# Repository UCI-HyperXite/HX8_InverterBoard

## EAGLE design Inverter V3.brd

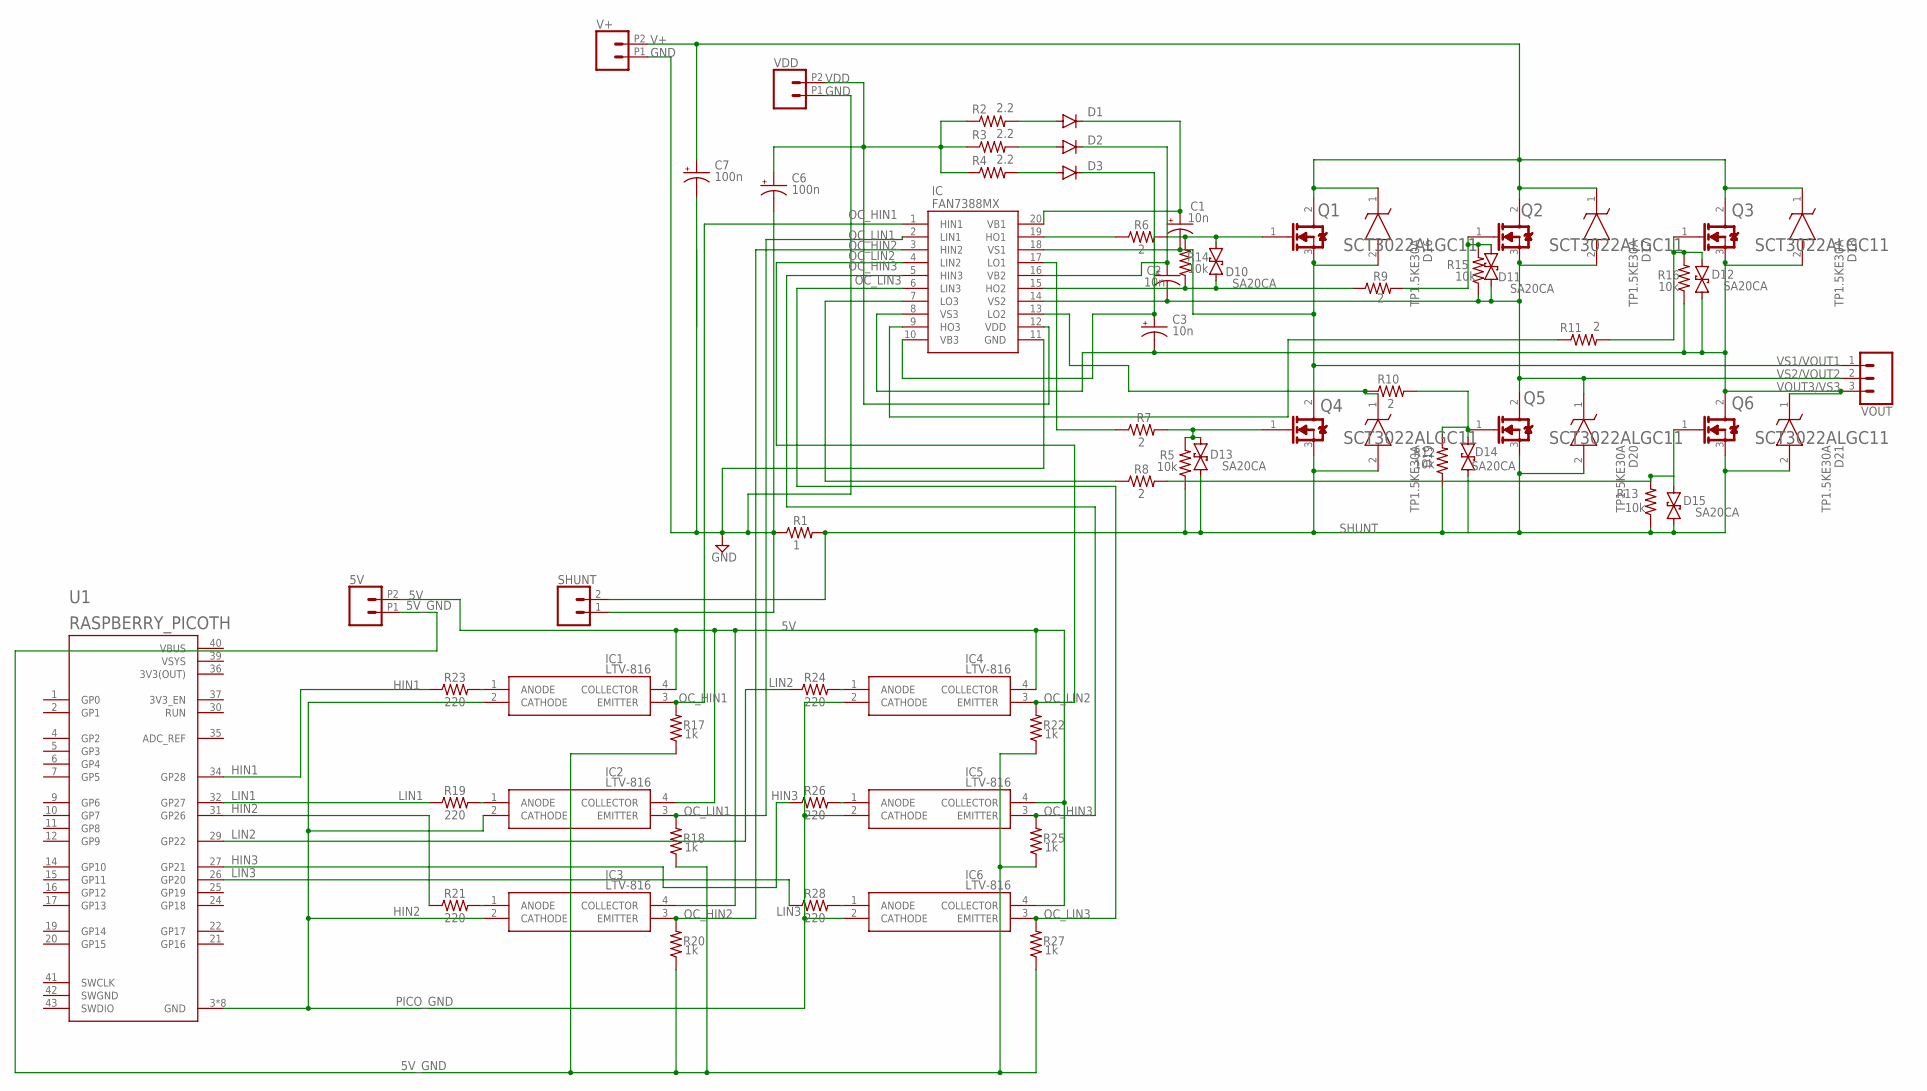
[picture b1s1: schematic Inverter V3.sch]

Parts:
5V: CONN_022.54MM_SCREWTERM; 1X02_2.54_SCREWTERM
C1, C2, C3: 10n; SMC_Z
C6: 100n; SMC_Z
C7: 100n; E5-5
D1, D2, D3: DIODE-GF1; GF1
D10, D11, D12, D13, D14, D15: SA20CA; CB417-15
D16, D17, D18, D19, D20, D21: TP1.5KE30A; DIOAD2855W107L835D505
IC: FAN7388MX; SOIC127P1032X265-20N
IC1, IC2, IC3, IC4, IC5, IC6: LTV-816; DIP762W60P254L460H450Q4N
Q1, Q2, Q3, Q4, Q5, Q6: ROHM_SCT3022ALGC11ROHM_SCT3022ALGC11_0_0; ROHM_SCT3022ALGC11_0
R1: 1; 0207/10
R2, R3, R4: 2.2; 0603
R5, R12, R13, R14, R15, R16: 10k; 0603
R6, R7, R8, R9, R10, R11: 2; 0603
R17, R18, R20, R22, R25, R27: 1k; 0603
R19, R21, R23, R24, R26, R28: 220; 0603
SHUNT: CONN_02PTH4; 1X02_XTRA_BIG
U1: RASPBERRY_PICOTH; PICO-PKG-TH
V+: CONN_022.54MM_SCREWTERM; 1X02_2.54_SCREWTERM
VDD: CONN_022.54MM_SCREWTERM; 1X02_2.54_SCREWTERM
VOUT: CONN_03SCREW-NS; SCREWTERMINAL-3.5MM-3-NS

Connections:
3V3(OUT): U1.36 (3V3(OUT))
5V: 5V.P2 (2), IC1.4 (COLLECTOR), IC2.4 (COLLECTOR), IC3.4 (COLLECTOR), IC4.4 (COLLECTOR), IC5.4 (COLLECTOR), IC6.4 (COLLECTOR)
5V_GND: 5V.P1 (1), R17.1, R18.1, R20.1, R22.1, R25.1, R27.1
GND: C6.-, C7.-, IC.11 (GND), R1.1, SHUNT.1, V+.P1 (1), VDD.P1 (1)
HIN1: R23.1, U1.34 (GP28)
HIN2: R21.1, U1.31 (GP26)
HIN3: R26.1, U1.27 (GP21)
HO1: IC.19 (HO1), R6.1
HO2: D10.A (1), IC.15 (HO2), R9.1, R14.1
HO3: IC.9 (HO3), R11.1
LIN1: R19.1, U1.32 (GP27)
LIN2: R24.1, U1.29 (GP22)
LIN3: R28.1, U1.26 (GP20)
LO1: IC.17 (LO1), R7.1
LO2: D19.1 (K), IC.13 (LO2), R10.1
LO3: IC.7 (LO3), R8.1
unnamed: IC3.1 (ANODE), R21.2
unnamed: IC2.1 (ANODE), R19.2
unnamed: IC1.1 (ANODE), R23.2
unnamed: IC4.1 (ANODE), R24.2
unnamed: IC5.1 (ANODE), R26.2
unnamed: IC6.1 (ANODE), R28.2
unnamed: D1.A, R2.2
unnamed: D2.A, R3.2
unnamed: D3.A, R4.2
OC_HIN1: IC.1 (HIN1), IC1.3 (EMITTER), R17.2
OC_HIN2: IC.3 (HIN2), IC3.3 (EMITTER), R20.2
OC_HIN3: IC.5 (HIN3), IC5.3 (EMITTER), R25.2
OC_LIN1: IC.2 (LIN1), IC2.3 (EMITTER), R18.2
OC_LIN2: IC.4 (LIN2), IC4.3 (EMITTER), R22.2
OC_LIN3: IC.6 (LIN3), IC6.3 (EMITTER), R27.2
PICO_GND: IC1.2 (CATHODE), IC2.2 (CATHODE), IC3.2 (CATHODE), IC4.2 (CATHODE), IC5.2 (CATHODE), IC6.2 (CATHODE), U1.3 (GND), U1.8 (GND), U1.13 (GND), U1.18 (GND), U1.23 (GND), U1.28 (GND), U1.33 (GND), U1.38 (GND)
SHUNT: D13.A (1), D14.A (1), D15.A (1), D19.2 (A), D20.2 (A), D21.2 (A), Q4.3 (SOURCE), Q5.3 (SOURCE), Q6.3 (SOURCE), R1.2, R5.1, R12.1, R13.1, SHUNT.2
SWGND: U1.42 (SWGND)
V+: C7.+, D16.1 (K), D17.1 (K), D18.1 (K), Q1.2 (DRAIN), Q2.2 (DRAIN), Q3.2 (DRAIN), V+.P2 (2)
VB1: C1.+, D1.C, IC.20 (VB1)
VB2: C2.+, D2.C, IC.16 (VB2)
VB3: C3.+, D3.C, IC.10 (VB3)
VBUS: U1.40 (VBUS)
VDD: C6.+, IC.12 (VDD), R2.1, R3.1, R4.1, VDD.P2 (2)
VGIN1: D10.C (2), Q1.1 (GATE), R6.2, R14.2
VGIN2: D11.C (2), Q2.1 (GATE), R9.2, R15.2
VGIN3: D12.C (2), Q3.1 (GATE), R11.2, R16.2
VGIN4: D13.C (2), Q4.1 (GATE), R5.2, R7.2
VGIN5: D14.C (2), Q5.1 (GATE), R10.2, R12.2
VGIN6: D15.C (2), Q6.1 (GATE), R8.2, R13.2
VOUT3/VS3: C3.-, D12.A (1), D18.2 (A), D21.1 (K), IC.8 (VS3), Q3.3 (SOURCE), Q6.2 (DRAIN), R16.1, VOUT.3
VS1/VOUT1: C1.-, D16.2 (A), IC.18 (VS1), Q1.3 (SOURCE), Q4.2 (DRAIN), VOUT.1
VS2/VOUT2: C2.-, D11.A (1), D17.2 (A), D20.1 (K), IC.14 (VS2), Q2.3 (SOURCE), Q5.2 (DRAIN), R15.1, VOUT.2
VSYS: U1.39 (VSYS)

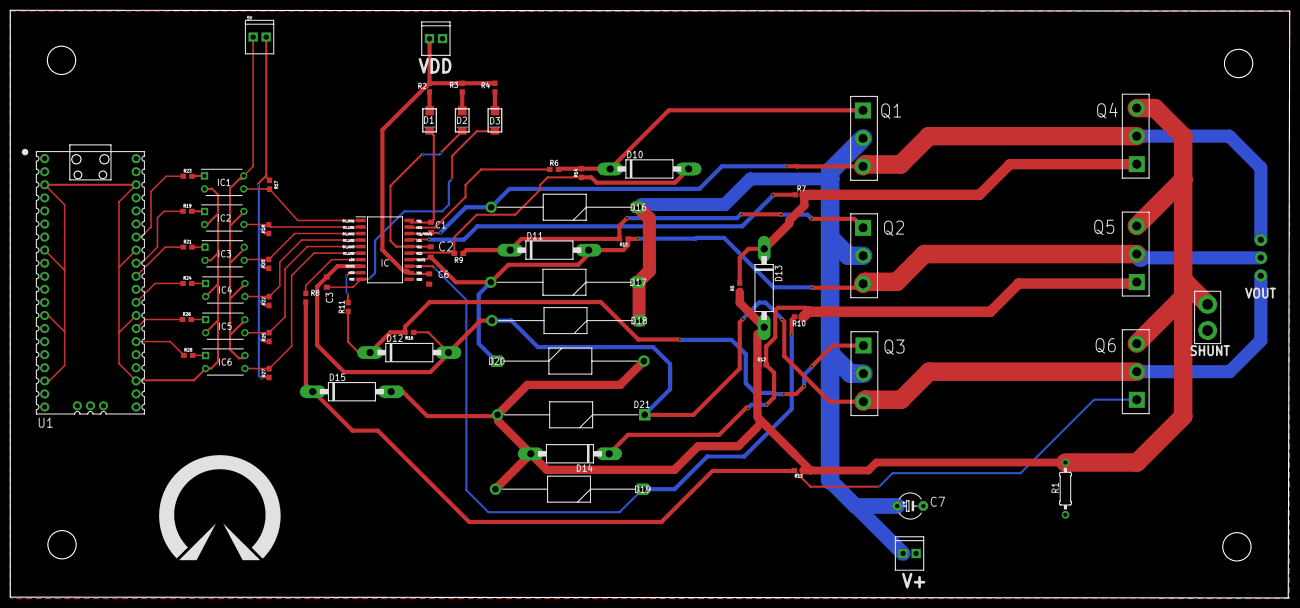
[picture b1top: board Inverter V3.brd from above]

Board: 2 copper layers, 248.6 x 114.2 mm, 67 parts (0 on the bottom side), 46 nets.

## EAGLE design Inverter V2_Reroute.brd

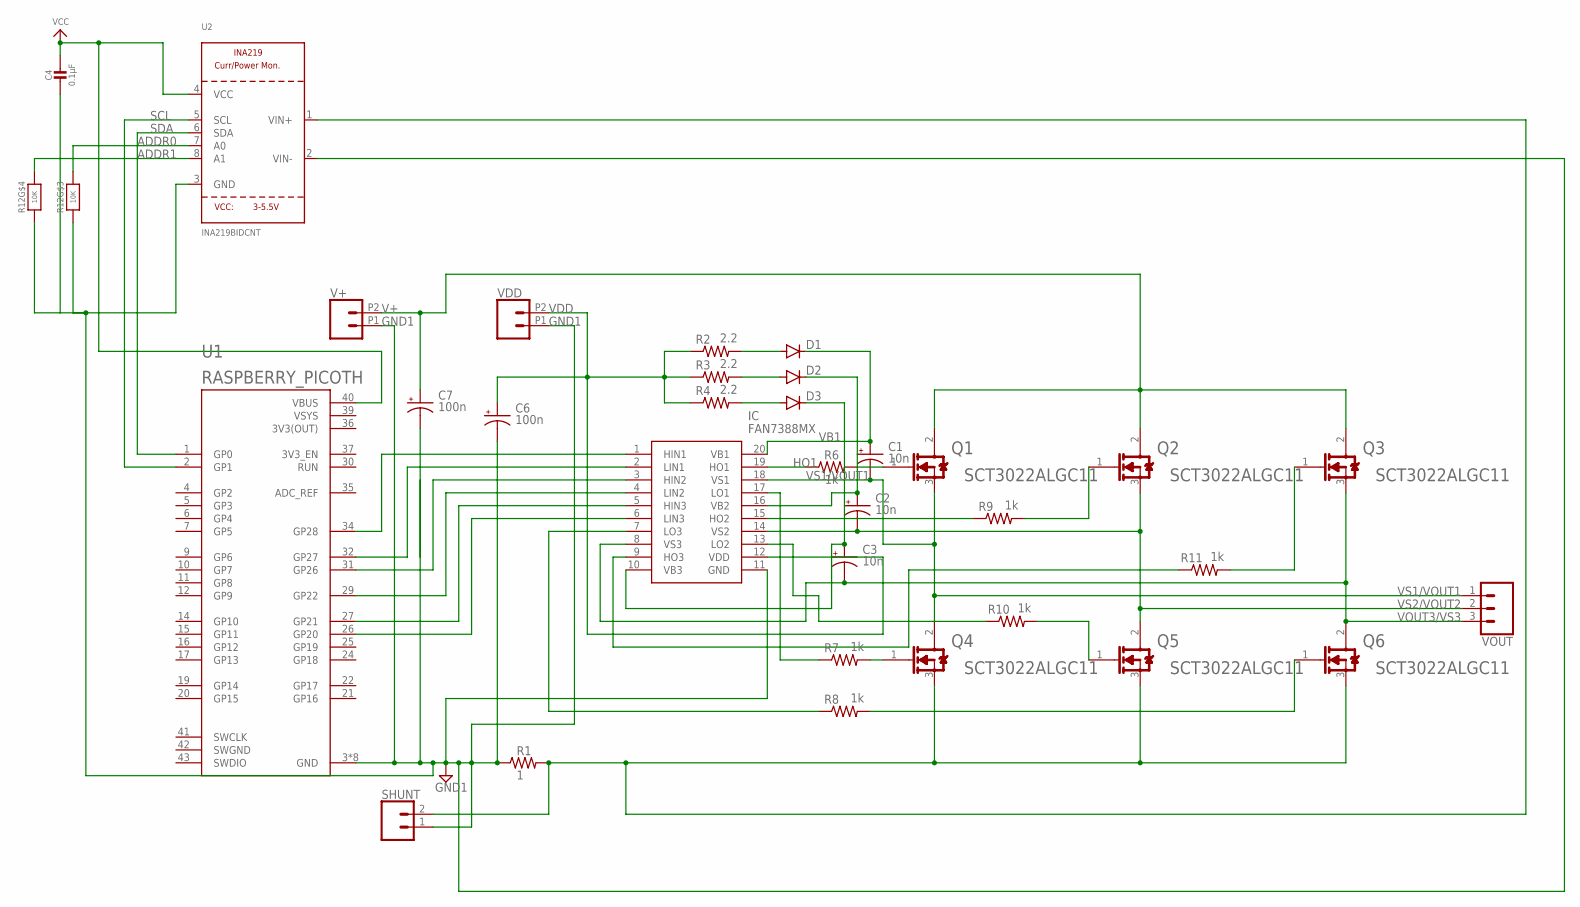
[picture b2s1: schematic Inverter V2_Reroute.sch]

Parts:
C1, C2, C3: 10n; SMC_Z
C4: 0.1µF; 0603-NO
C6: 100n; SMC_Z
C7: 100n; E5-5
D1, D2, D3: DIODE-GF1; GF1
IC: FAN7388MX; SOIC127P1032X265-20N
Q1, Q2, Q3, Q4, Q5, Q6: ROHM_SCT3022ALGC11ROHM_SCT3022ALGC11_0_0; ROHM_SCT3022ALGC11_0
R1: 1; 0207/10
R2, R3, R4: 2.2; 0603
R6, R7, R8, R9, R10, R11: 1k; 0603
R12: 10K; RESPACK_4X0603
SHUNT: CONN_02PTH4; 1X02_XTRA_BIG
U1: RASPBERRY_PICOTH; PICO-PKG-TH
U2: INA219BIDCNT; SOT23-8
V+: CONN_022.54MM_SCREWTERM; 1X02_2.54_SCREWTERM
VDD: CONN_022.54MM_SCREWTERM; 1X02_2.54_SCREWTERM
VOUT: CONN_03SCREW-NS; SCREWTERMINAL-3.5MM-3-NS

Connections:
3V3(OUT): U1.36 (3V3(OUT))
ADDR0: R12.6 (2), U2.7 (A0)
ADDR1: R12.5 (2), U2.8 (A1)
GND1: C4.2, C6.-, C7.-, IC.11 (GND), R1.1, R12.3 (1), R12.4 (1), SHUNT.1, U1.3 (GND), U1.8 (GND), U1.13 (GND), U1.18 (GND), U1.23 (GND), U1.28 (GND), U1.33 (GND), U1.38 (GND), U2.2 (VIN-), U2.3 (GND), V+.P1 (1), VDD.P1 (1)
HIN1: IC.1 (HIN1), U1.34 (GP28)
HIN3: IC.5 (HIN3), U1.27 (GP21)
HO1: IC.19 (HO1), R6.1
HO2: IC.15 (HO2), R9.1
HO3: IC.9 (HO3), R11.1
LIN1: IC.2 (LIN1), U1.32 (GP27)
LIN2: IC.4 (LIN2), U1.29 (GP22)
LIN3: IC.6 (LIN3), U1.26 (GP20)
LO1: IC.17 (LO1), R7.1
LO2: IC.13 (LO2), R10.1
LO3: IC.7 (LO3), R8.1
unnamed: IC.3 (HIN2), U1.31 (GP26)
unnamed: D1.A, R2.2
unnamed: D2.A, R3.2
unnamed: D3.A, R4.2
SCL: U1.2 (GP1), U2.5 (SCL)
SDA: U1.1 (GP0), U2.6 (SDA)
SHUNT: Q4.3 (SOURCE), Q5.3 (SOURCE), Q6.3 (SOURCE), R1.2, SHUNT.2, U2.1 (VIN+)
SWGND: U1.42 (SWGND)
V+: C7.+, Q1.2 (DRAIN), Q2.2 (DRAIN), Q3.2 (DRAIN), V+.P2 (2)
VB1: C1.+, D1.C, IC.20 (VB1)
VB2: C2.+, D2.C, IC.16 (VB2)
VB3: C3.+, D3.C, IC.10 (VB3)
VCC: C4.1, U1.40 (VBUS), U2.4 (VCC)
VDD: C6.+, IC.12 (VDD), R2.1, R3.1, R4.1, VDD.P2 (2)
VGIN1: Q1.1 (GATE), R6.2
VGIN2: Q2.1 (GATE), R9.2
VGIN3: Q3.1 (GATE), R11.2
VGIN4: Q4.1 (GATE), R7.2
VGIN5: Q5.1 (GATE), R10.2
VGIN6: Q6.1 (GATE), R8.2
VOUT3/VS3: C3.-, IC.8 (VS3), Q3.3 (SOURCE), Q6.2 (DRAIN), VOUT.3
VS1/VOUT1: C1.-, IC.18 (VS1), Q1.3 (SOURCE), Q4.2 (DRAIN), VOUT.1
VS2/VOUT2: C2.-, IC.14 (VS2), Q2.3 (SOURCE), Q5.2 (DRAIN), VOUT.2
VSYS: U1.39 (VSYS)

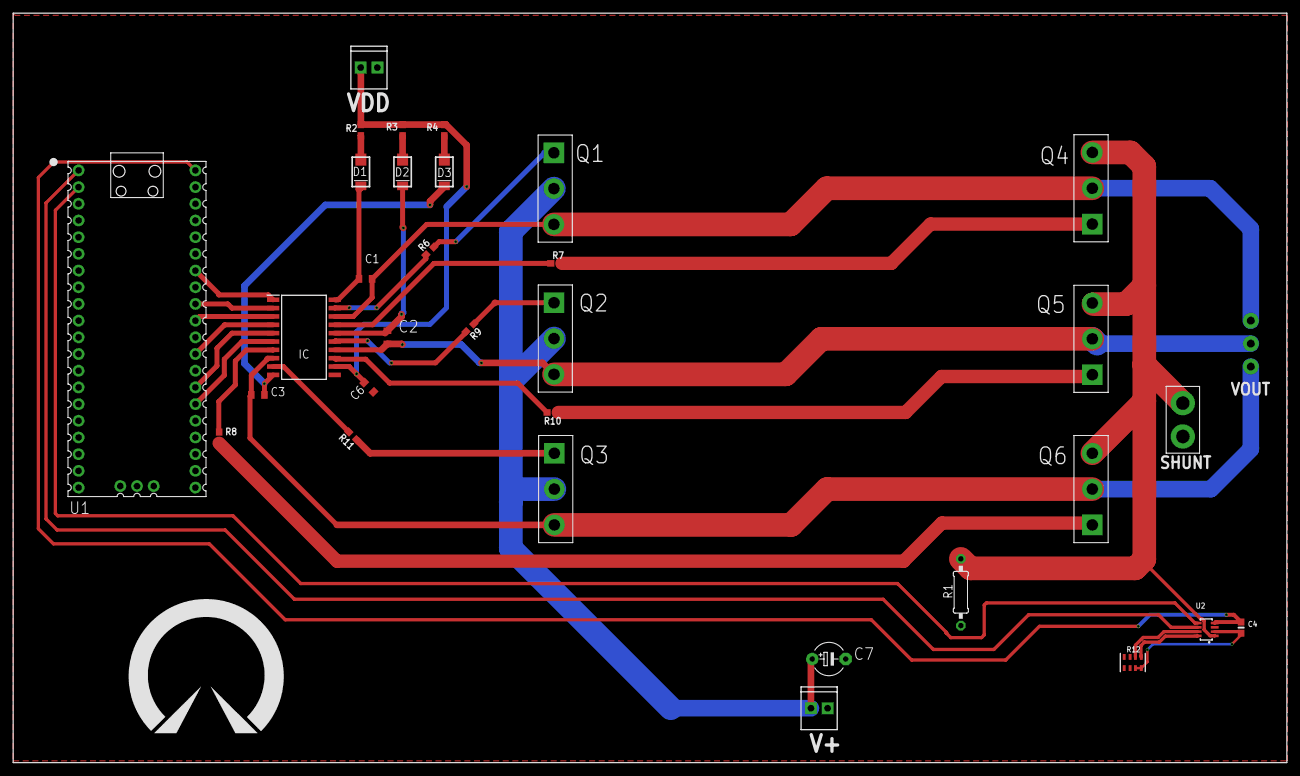
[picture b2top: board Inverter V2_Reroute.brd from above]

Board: 2 copper layers, 193.8 x 114.0 mm, 33 parts (0 on the bottom side), 36 nets.

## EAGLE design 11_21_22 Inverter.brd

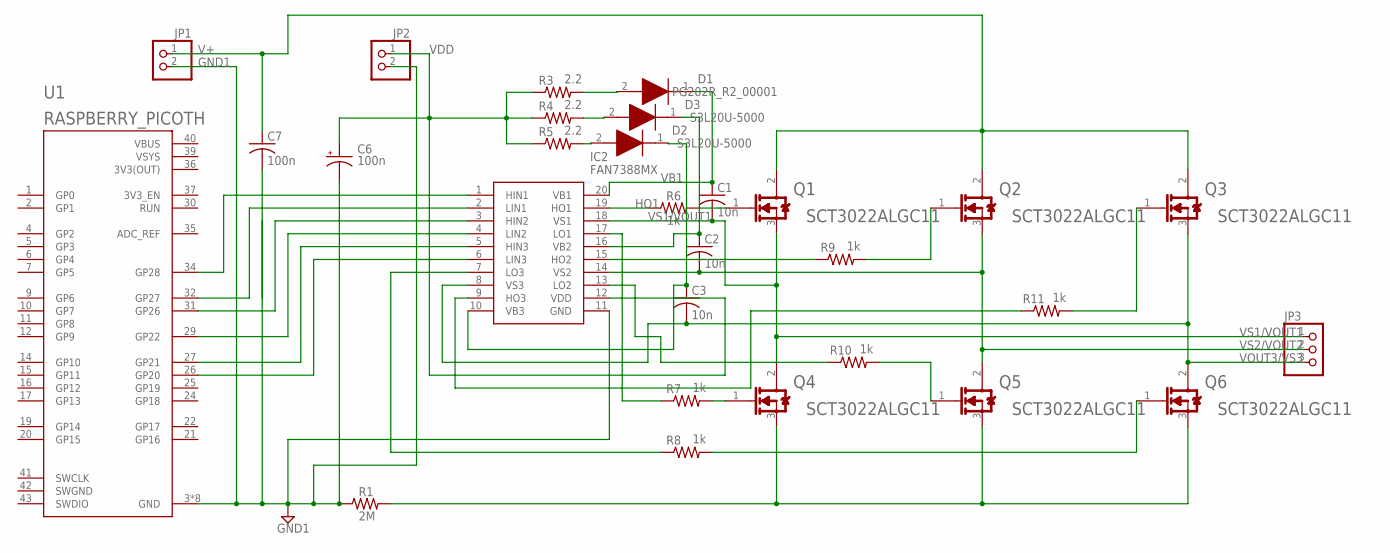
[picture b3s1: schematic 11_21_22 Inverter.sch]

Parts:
C1, C2, C3: 10n; C025-024X044
C6: 100n; SMC_Z
C7: 100n; C025-024X044
D1: PG202R_R2_00001; DIOAD2460W140L700D440; MANUFACTURER_PART_NUMBER PG202R_R2_00001; MOUSER_PART_NUMBER PG202R_R2_00001
D2, D3: S3L20U-5000; DIOAD2460W140L700D440
IC2: FAN7388MX; SOIC127P1032X265-20N
JP1, JP2: PINHD-1X2; 1X02
JP3: PINHD-1X3; 1X03
Q1, Q2, Q3, Q4, Q5, Q6: ROHM_SCT3022ALGC11ROHM_SCT3022ALGC11_0_0; ROHM_SCT3022ALGC11_0
R1: 2M; 0207/10
R3, R4, R5: 2.2; 0207/10
R6, R7, R8, R9, R10, R11: 1k; 0603
U1: RASPBERRY_PICOTH; PICO-PKG-TH

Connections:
3V3(OUT): U1.36 (3V3(OUT))
COM/GND: Q4.3 (SOURCE), Q5.3 (SOURCE), Q6.3 (SOURCE), R1.2
GND1: C6.-, C7.2, IC2.11 (GND), JP1.2, JP2.2, R1.1, U1.3 (GND), U1.8 (GND), U1.13 (GND), U1.18 (GND), U1.23 (GND), U1.28 (GND), U1.33 (GND), U1.38 (GND)
HO1: IC2.19 (HO1), R6.1
HO2: IC2.15 (HO2), R9.1
LO2: IC2.13 (LO2), R10.1
LO3: IC2.7 (LO3), R8.1
unnamed: IC2.1 (HIN1), U1.34 (GP28)
unnamed: IC2.17 (LO1), R7.1
unnamed: IC2.2 (LIN1), U1.32 (GP27)
unnamed: IC2.3 (HIN2), U1.31 (GP26)
unnamed: IC2.4 (LIN2), U1.29 (GP22)
unnamed: Q1.1 (GATE), R6.2
unnamed: IC2.5 (HIN3), U1.27 (GP21)
unnamed: Q5.1 (GATE), R10.2
unnamed: IC2.6 (LIN3), U1.26 (GP20)
unnamed: Q3.1 (GATE), R11.2
unnamed: Q2.1 (GATE), R9.2
unnamed: IC2.9 (HO3), R11.1
unnamed: Q6.1 (GATE), R8.2
unnamed: Q4.1 (GATE), R7.2
unnamed: D1.2 (A), R3.2
unnamed: D3.2 (A), R4.2
unnamed: D2.2 (A), R5.2
SWGND: U1.42 (SWGND)
V+: C7.1, JP1.1, Q1.2 (DRAIN), Q2.2 (DRAIN), Q3.2 (DRAIN)
VB1: C1.1, D1.1 (K), IC2.20 (VB1)
VB2: C2.1, D3.1 (K), IC2.16 (VB2)
VB3: C3.1, D2.1 (K), IC2.10 (VB3)
VBUS: U1.40 (VBUS)
VDD: C6.+, IC2.12 (VDD), JP2.1, R3.1, R4.1, R5.1
VOUT3/VS3: C3.2, IC2.8 (VS3), JP3.3, Q3.3 (SOURCE), Q6.2 (DRAIN)
VS1/VOUT1: C1.2, IC2.18 (VS1), JP3.1, Q1.3 (SOURCE), Q4.2 (DRAIN)
VS2/VOUT2: C2.2, IC2.14 (VS2), JP3.2, Q2.3 (SOURCE), Q5.2 (DRAIN)
VSYS: U1.39 (VSYS)

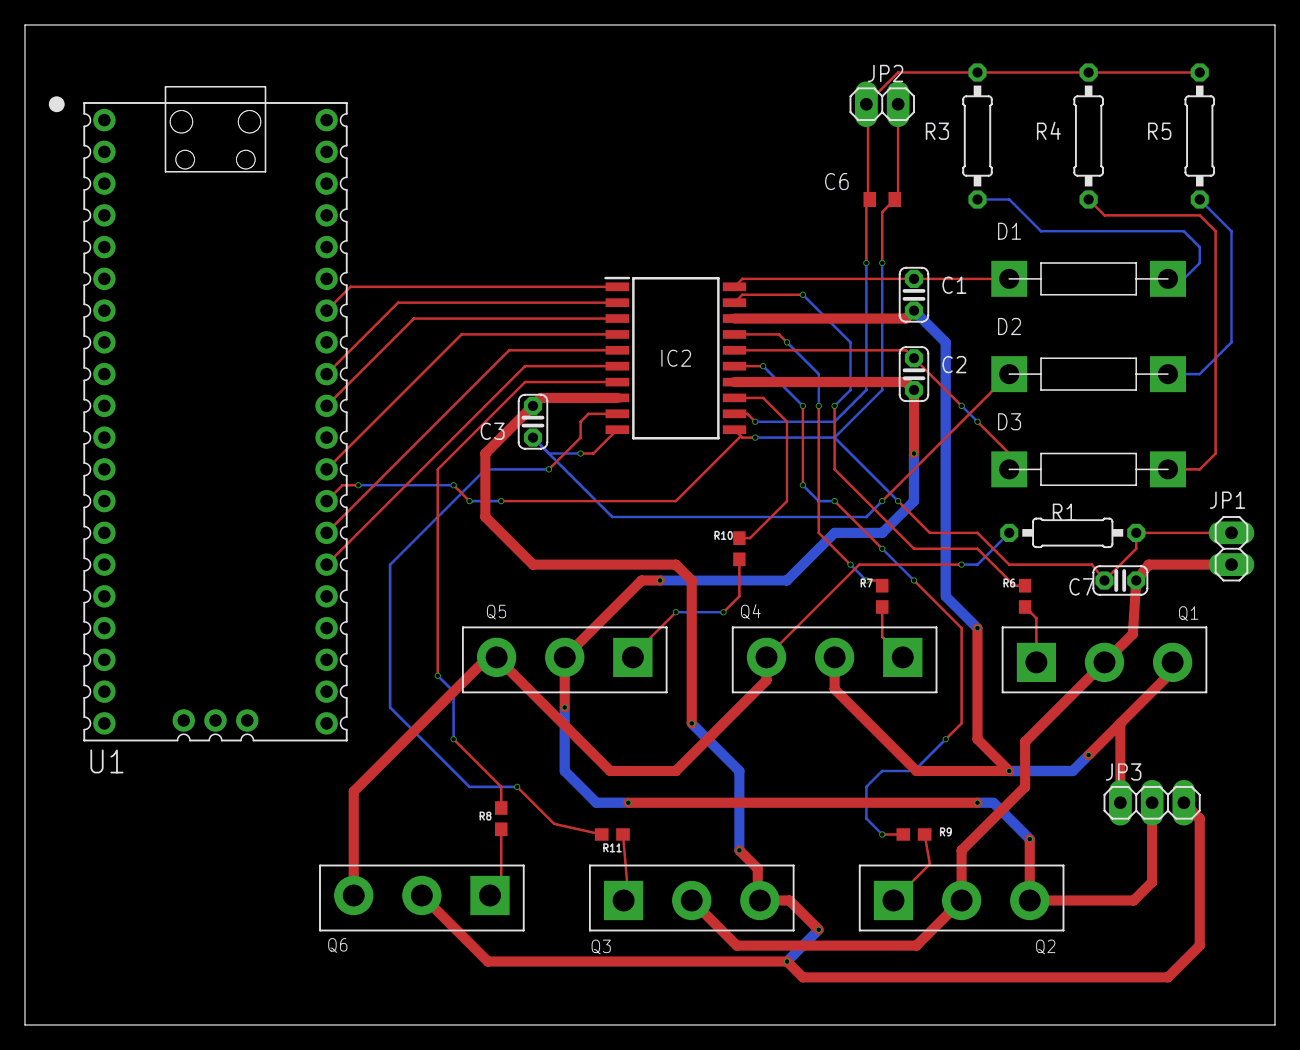
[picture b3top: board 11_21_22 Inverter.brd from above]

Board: 2 copper layers, 100.0 x 80.0 mm, 29 parts (0 on the bottom side), 31 nets.

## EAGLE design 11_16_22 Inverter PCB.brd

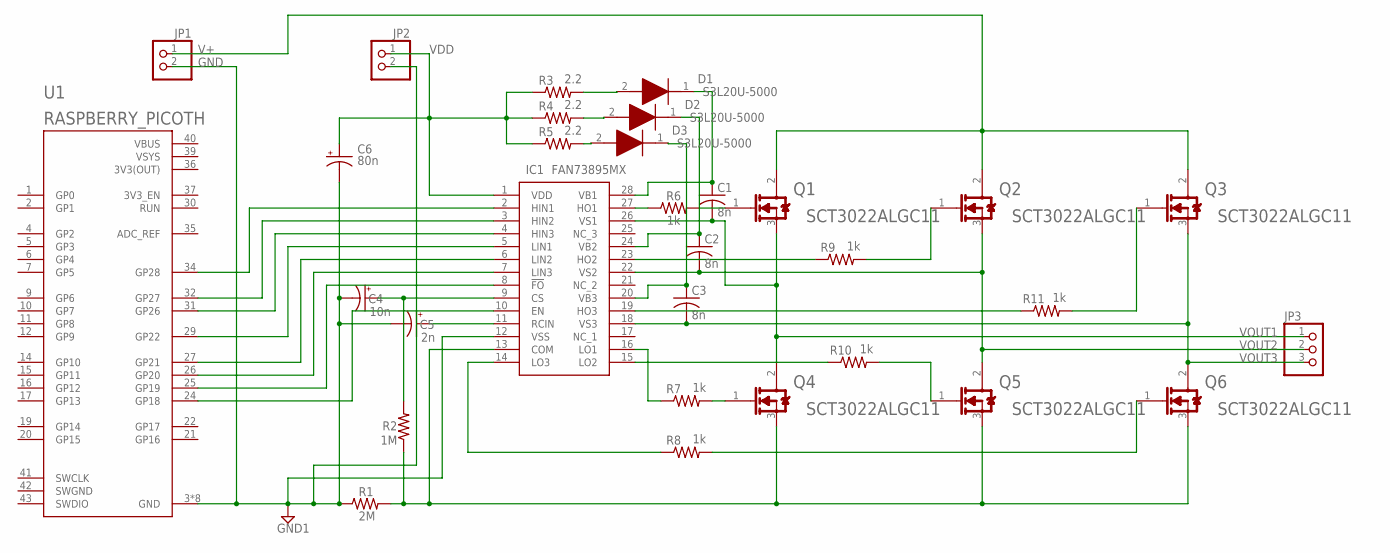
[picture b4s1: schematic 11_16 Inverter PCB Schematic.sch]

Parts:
C1, C2, C3: 8n; C025-024X044
C4: 10n; SMC_Z
C5: 2n; SMC_Z
C6: 80n; SMC_Z
D1, D2, D3: S3L20U-5000; DIOAD2460W140L700D440
IC1: FAN73895MX; SOIC127P1031X265-28N
JP1, JP2: PINHD-1X2; 1X02
JP3: PINHD-1X3; 1X03
Q1, Q2, Q3, Q4, Q5, Q6: ROHM_SCT3022ALGC11ROHM_SCT3022ALGC11_0_0; ROHM_SCT3022ALGC11_0
R1: 2M; 0207/10
R2: 1M; 0207/10
R3, R4, R5: 2.2; 0207/10
R6, R7, R8, R9, R10, R11: 1k; 0603
U1: RASPBERRY_PICOTH; PICO-PKG-TH

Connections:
3V3(OUT): U1.36 (3V3(OUT))
GND: C4.-, C5.-, C6.-, IC1.12 (VSS), JP1.2, JP2.2, R1.1, U1.3 (GND), U1.8 (GND), U1.13 (GND), U1.18 (GND), U1.23 (GND), U1.28 (GND), U1.33 (GND), U1.38 (GND)
unnamed: IC1.2 (HIN1), U1.34 (GP28)
unnamed: IC1.13 (COM), Q4.3 (SOURCE), Q5.3 (SOURCE), Q6.3 (SOURCE), R1.2, R2.1
unnamed: IC1.19 (HO3), R11.1
unnamed: IC1.27 (HO1), R6.1
unnamed: IC1.8 (!FO), U1.25 (GP19)
unnamed: Q1.1 (GATE), R6.2
unnamed: IC1.16 (LO1), R7.1
unnamed: Q5.1 (GATE), R10.2
unnamed: IC1.14 (LO3), R8.1
unnamed: Q3.1 (GATE), R11.2
unnamed: Q2.1 (GATE), R9.2
unnamed: IC1.10 (EN), U1.24 (GP18)
unnamed: IC1.23 (HO2), R9.1
unnamed: Q6.1 (GATE), R8.2
unnamed: IC1.15 (LO2), R10.1
unnamed: Q4.1 (GATE), R7.2
unnamed: C1.1, D1.1 (K), IC1.28 (VB1)
unnamed: C2.1, D2.1 (K), IC1.24 (VB2)
unnamed: C3.1, D3.1 (K), IC1.20 (VB3)
unnamed: IC1.3 (HIN2), U1.32 (GP27)
unnamed: C5.+, IC1.11 (RCIN)
unnamed: IC1.4 (HIN3), U1.31 (GP26)
unnamed: IC1.5 (LIN1), U1.29 (GP22)
unnamed: IC1.6 (LIN2), U1.27 (GP21)
unnamed: IC1.7 (LIN3), U1.26 (GP20)
unnamed: D1.2 (A), R3.2
unnamed: C4.+, IC1.9 (CS), R2.2
unnamed: D2.2 (A), R4.2
unnamed: D3.2 (A), R5.2
SWGND: U1.42 (SWGND)
V+: JP1.1, Q1.2 (DRAIN), Q2.2 (DRAIN), Q3.2 (DRAIN)
VBUS: U1.40 (VBUS)
VDD: C6.+, IC1.1 (VDD), JP2.1, R3.1, R4.1, R5.1
VOUT1: C1.2, IC1.26 (VS1), JP3.1, Q1.3 (SOURCE), Q4.2 (DRAIN)
VOUT2: C2.2, IC1.22 (VS2), JP3.2, Q2.3 (SOURCE), Q5.2 (DRAIN)
VOUT3: C3.2, IC1.18 (VS3), JP3.3, Q3.3 (SOURCE), Q6.2 (DRAIN)
VSYS: U1.39 (VSYS)

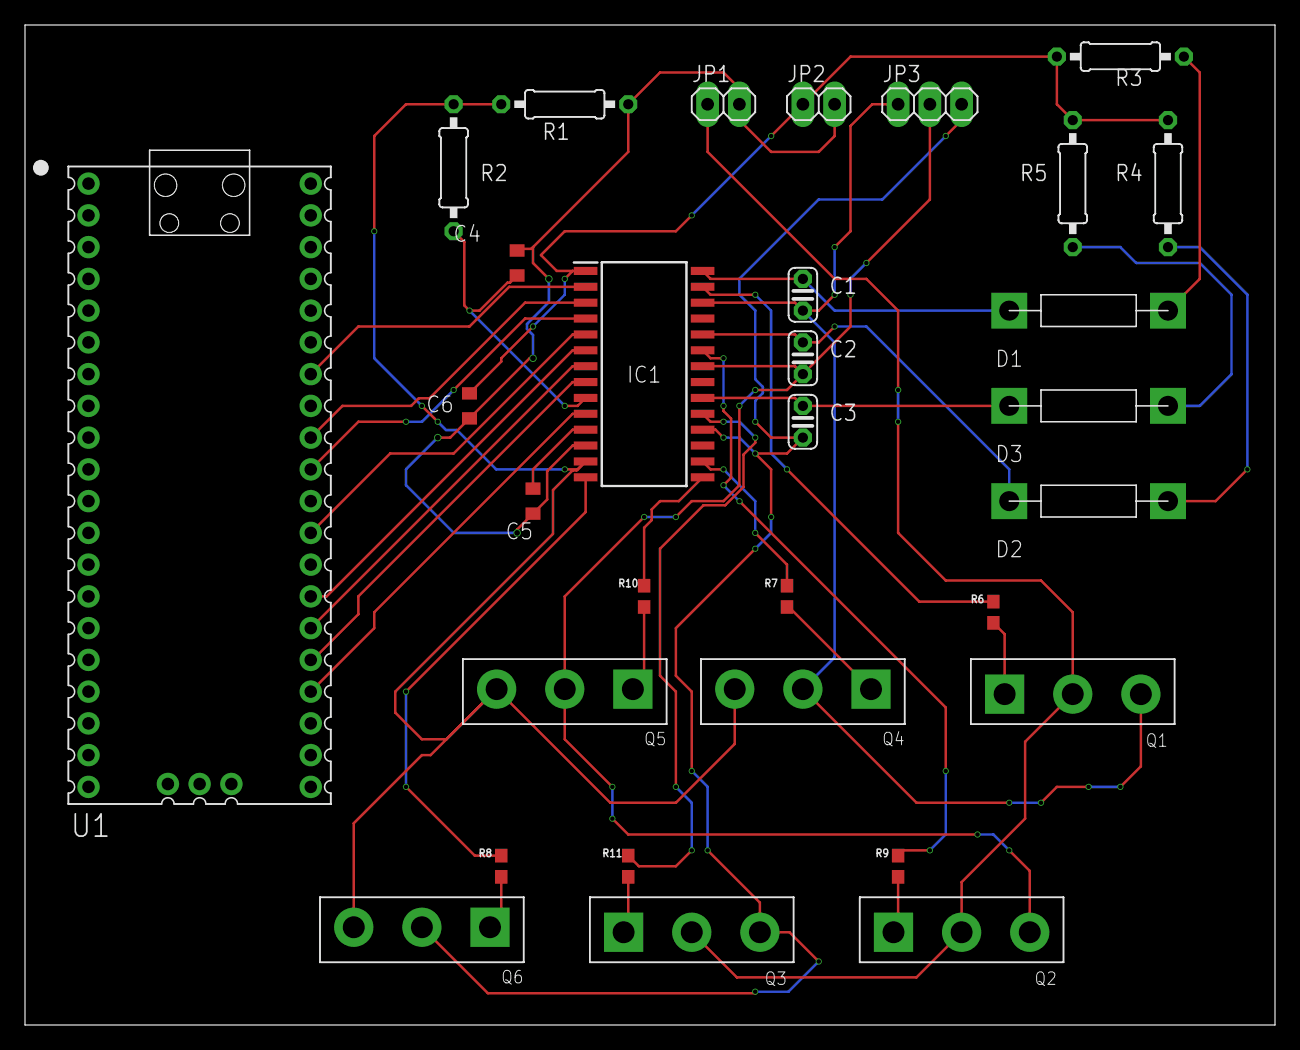
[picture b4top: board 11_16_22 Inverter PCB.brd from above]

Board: 2 copper layers, 100.0 x 80.0 mm, 31 parts (0 on the bottom side), 35 nets.

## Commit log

2022-11-16 Add first version of PCB for inverter
2022-11-17 Add schematic and gerber files
2022-11-17 Rename gerber files folder
2022-11-21 Fixing schematic and PCB, adding gerber files
2022-11-22 Updated inverter board and schematic with new IC
2023-02-09 Inverter V2 initial files
2023-02-14 Routing Inverter V2
2023-02-15 Revision to routed V2 inverter
2023-02-15 Adjusted trace width + silkscreen
2023-02-24 Rerouted inverter to minimize analog signal for INA219
2023-04-14 Inverter V3
2023-04-27 Swapped flyback diodes and added silkscreen for IC pins

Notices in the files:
parts and their libraries:
SparkFun-Resistors: Licensing: Creative Commons ShareAlike 4.0 International - https://creativecommons.org/licenses/by-sa/4.0
